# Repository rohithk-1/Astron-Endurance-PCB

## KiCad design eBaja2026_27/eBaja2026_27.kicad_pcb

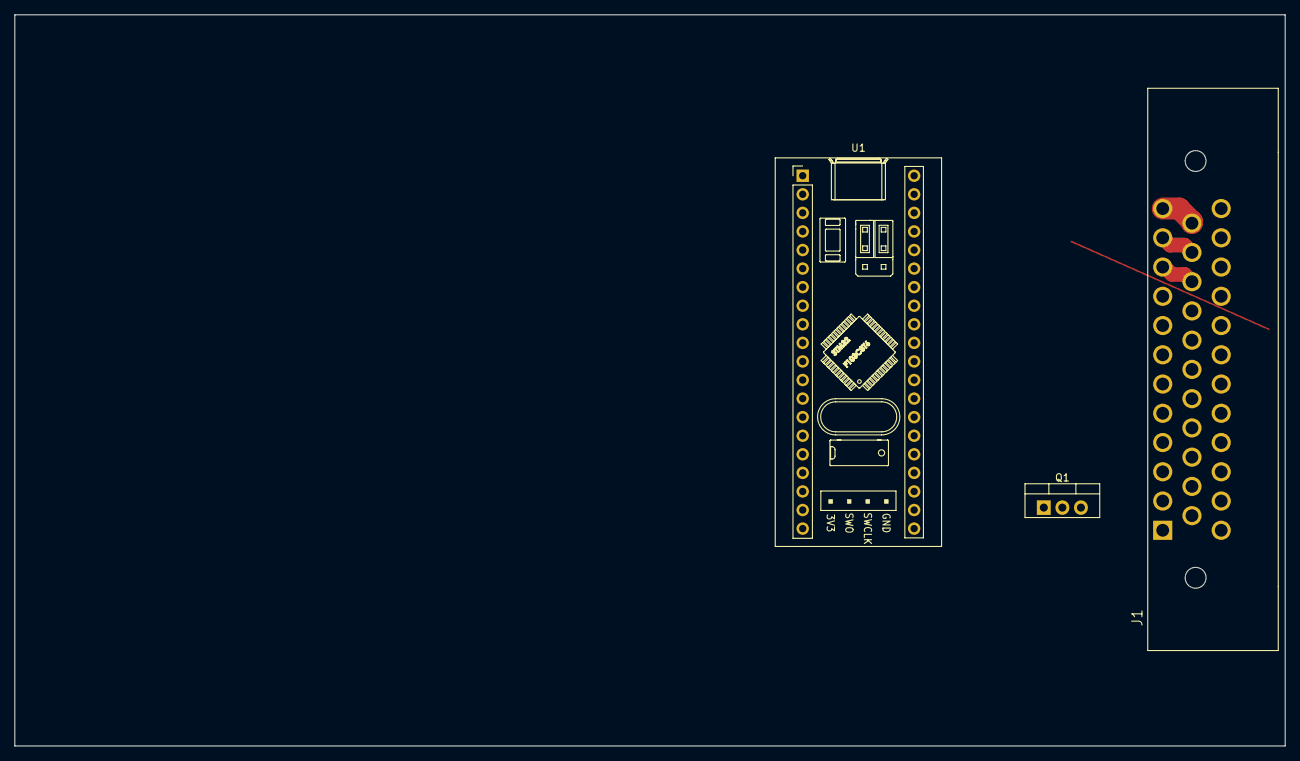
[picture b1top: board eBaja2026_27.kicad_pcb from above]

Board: 4 copper layers, 173.8 x 100.0 mm, 3 parts (0 on the bottom side), 4 nets.

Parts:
J1: 1-776163-1; TE_1-776163-1
Q1: IRF540N; TO-220-3_Vertical
U1: STM32_BluePill; YAAJ_BluePill_1

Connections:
3.3v: J1.10, J1.21
5v: J1.11, J1.22
12v: J1.12, J1.23
unnamed: Q1.1 (G_1), U1.29 (PA4_29)
